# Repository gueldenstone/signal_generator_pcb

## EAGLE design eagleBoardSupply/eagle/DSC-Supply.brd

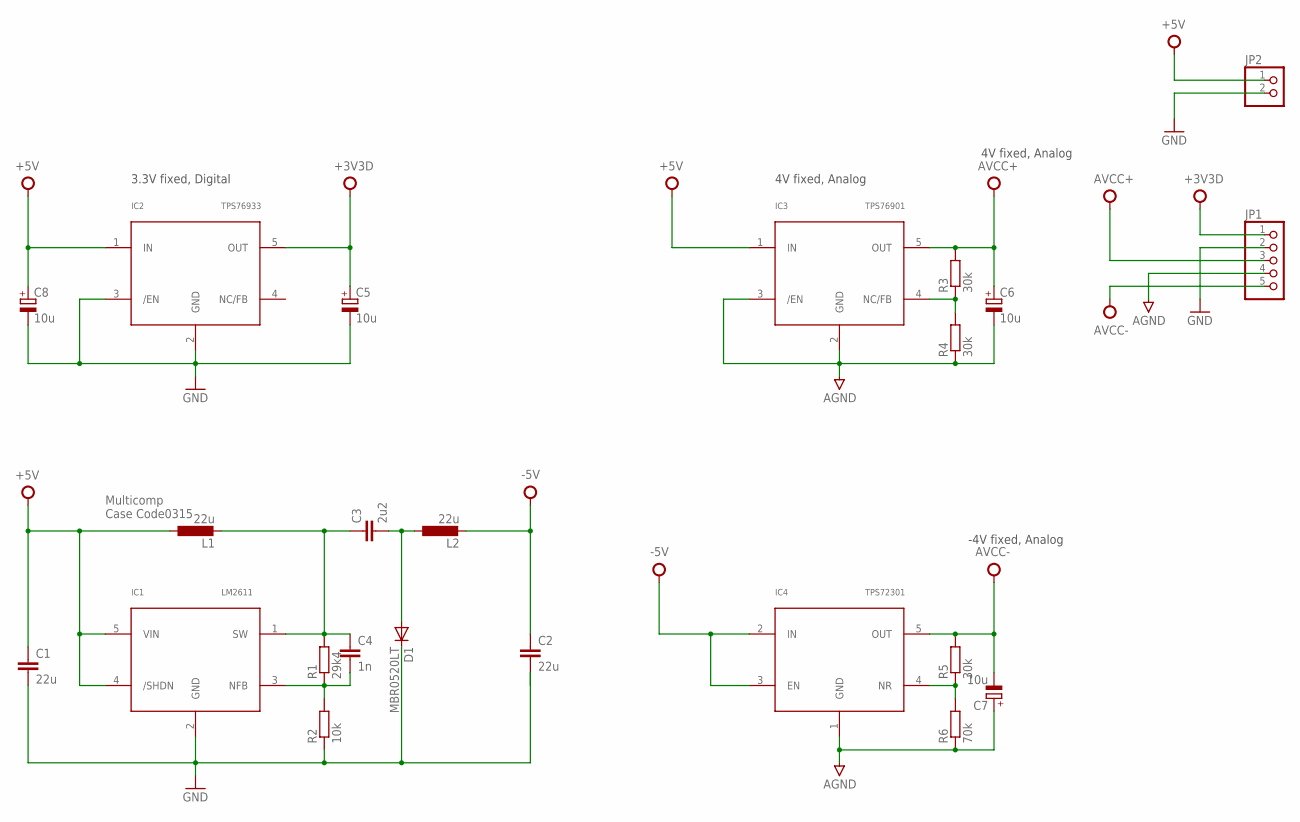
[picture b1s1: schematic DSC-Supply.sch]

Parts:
C1, C2: 22u; C0805
C3: 2u2; C0805
C4: 1n; C0805
C5, C6, C7, C8: 10u; 153CLV-0405
D1: MBR0520LT; SOD123
IC1: LM2611; SOT23-DBV
IC2: TPS76933; SOT23-DBV
IC3: TPS76901; SOT23-DBV
IC4: TPS72301; SOT23-DBV
JP1: PINHD-1X5; 1X05
JP2: PINHD-1X2; 1X02
L1, L2: 22u; L0315
R1: 29k4; R0805
R2: 10k; R0805
R3, R4, R5: 30k; R0805
R6: 70k; R0805

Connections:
+3V3D: C5.+, IC2.5 (OUT), JP1.1
+5V: C1.1, C8.+, IC1.4 (/SHDN), IC1.5 (VIN), IC2.1 (IN), IC3.1 (IN), JP2.1, L1.1
-5V: C2.1, IC4.2 (IN), IC4.3 (EN), L2.2
AGND: C6.-, C7.+, IC3.2 (GND), IC3.3 (/EN), IC4.1 (GND), JP1.4, R4.1, R6.1
AVCC+: C6.+, IC3.5 (OUT), JP1.3, R3.2
AVCC-: C7.-, IC4.5 (OUT), JP1.5, R5.2
GND: C1.2, C2.2, C5.-, C8.-, D1.C, IC1.2 (GND), IC2.2 (GND), IC2.3 (/EN), JP1.2, JP2.2, R2.1
unnamed: C3.1, C4.1, IC1.1 (SW), L1.2, R1.2
unnamed: C4.2, IC1.3 (NFB), R1.1, R2.2
unnamed: IC3.4 (NC/FB), R3.1, R4.2
unnamed: IC4.4 (NR), R5.1, R6.2
unnamed: C3.2, D1.A, L2.1

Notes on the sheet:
Multicomp Case Code0315
3.3V fixed, Digital
4V fixed, Analog
-4V fixed, Analog

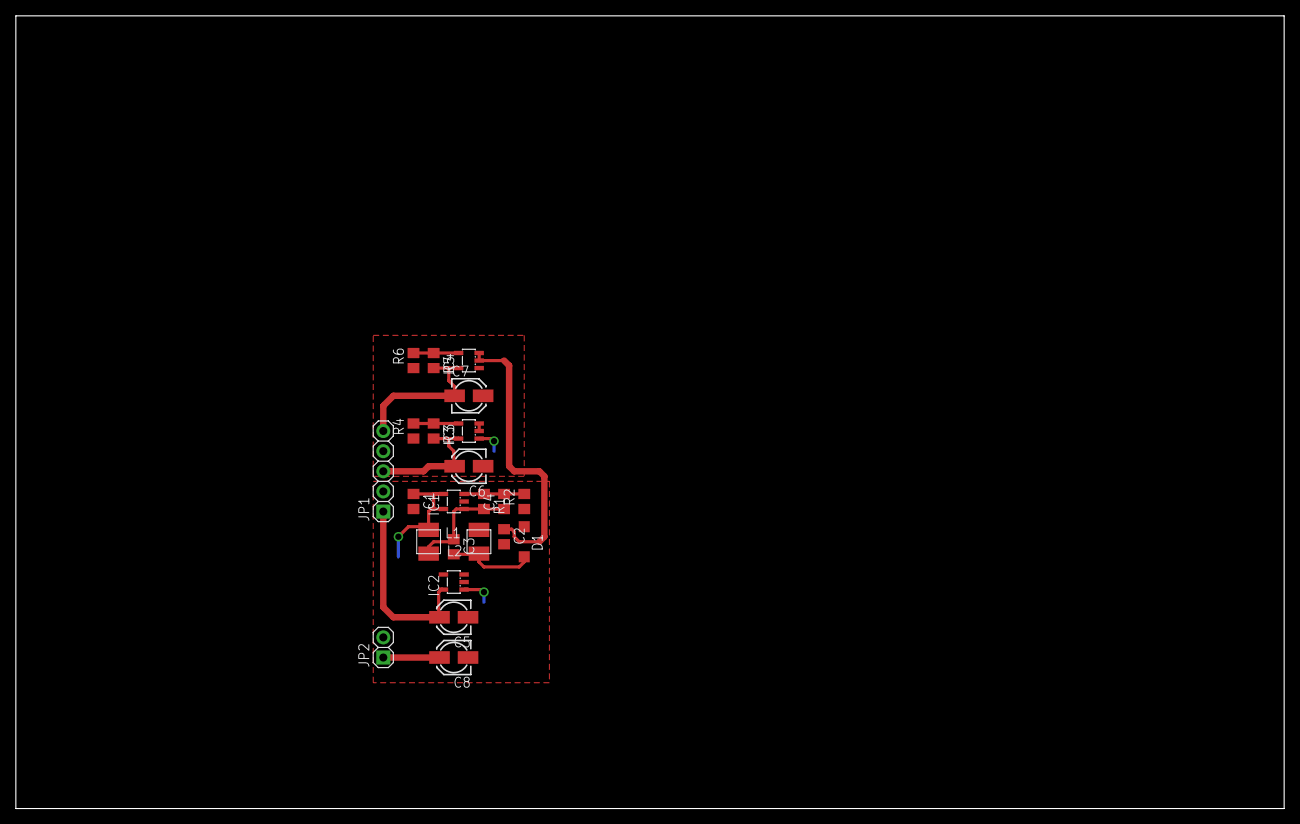
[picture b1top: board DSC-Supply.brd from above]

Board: 2 copper layers, 160.0 x 100.0 mm, 23 parts (0 on the bottom side), 12 nets.

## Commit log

2020-10-19 Version 1 with all libs
2020-10-29 new pcb design and pin layout
2020-11-02 added power supply, integrated in schematic
2020-11-07 finished PCB v1
2020-11-07 cleanup
2020-11-08 added author to pcb
2020-11-10 send to production
2020-12-09 final status
